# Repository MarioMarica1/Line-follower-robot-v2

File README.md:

# Line Follower Robot v2 · God of Cheese

Line follower robot hardware for **ROBOTEC UPT 2027**. This repository contains the **God of Cheese** KiCad project, its custom libraries, mechanical models, and existing fabrication exports.

The design includes an **ESP32-S3**, a **DRV8833** motor driver, a buck converter, battery connection, slide switch, and motor/sensor connections. Firmware is not included in this repository.

## PCB

| Front | Back (mirrored) |
| :---: | :---: |
|  |  |

These previews are generated from the committed PCB and show copper, silkscreen, and board outline.

## Schematic

[View or download the schematic PDF](docs/schematic.pdf).

## Open the project

1. Clone or download the entire repository.
2. Install **KiCad 10.0 or newer** with its standard symbol, footprint, and 3D model libraries.
3. Open [`God_of_cheeseLFR.kicad_pro`](God_of_cheeseLFR.kicad_pro) in the KiCad Project Manager.
4. Open the schematic or PCB from that project.

Designed in **KiCad 10.0**. Project-specific libraries use `${KIPRJMOD}` paths so the project can be opened from a different computer.

## Repository contents

| Path | Contents |
| --- | --- |
| `God_of_cheeseLFR.kicad_pro` | Main project and design settings |
| `God_of_cheeseLFR.kicad_sch` | Circuit schematic |
| `God_of_cheeseLFR.kicad_pcb` | Two-layer PCB layout |
| `*.pretty/` | Custom footprints, including board artwork |
| `symbols/` | Custom symbol libraries recovered from the schematic's embedded symbols |
| `3dmodels/` | STEP, STL, and SolidWorks mechanical assets |
| `fp-lib-table`, `sym-lib-table` | Portable project library tables |
| `docs/` | PCB previews, schematic PDF, and validation reports |
| `production/` | Existing Gerber archive, BOM, positions, designators, and IPC netlist |

## Design status

This is a hardware design snapshot. See [the validation notes](docs/validation.md) for checks run before publication and the outstanding findings.

The updated schematic includes the input supply `PWR_FLAG` and passes ERC with **0 errors**; 19 connection-grid warnings remain.

The files in `production/` and `Gerber/` are preserved exports supplied with the project; they were **not regenerated** for this upload and their correspondence to the current PCB has not been established. Review the current design and regenerate fabrication outputs before ordering boards. Some BOM entries still contain generic values and empty supplier part numbers.

Local backups, autosaves, editor history, caches, locks, and per-user KiCad settings are excluded from version control.

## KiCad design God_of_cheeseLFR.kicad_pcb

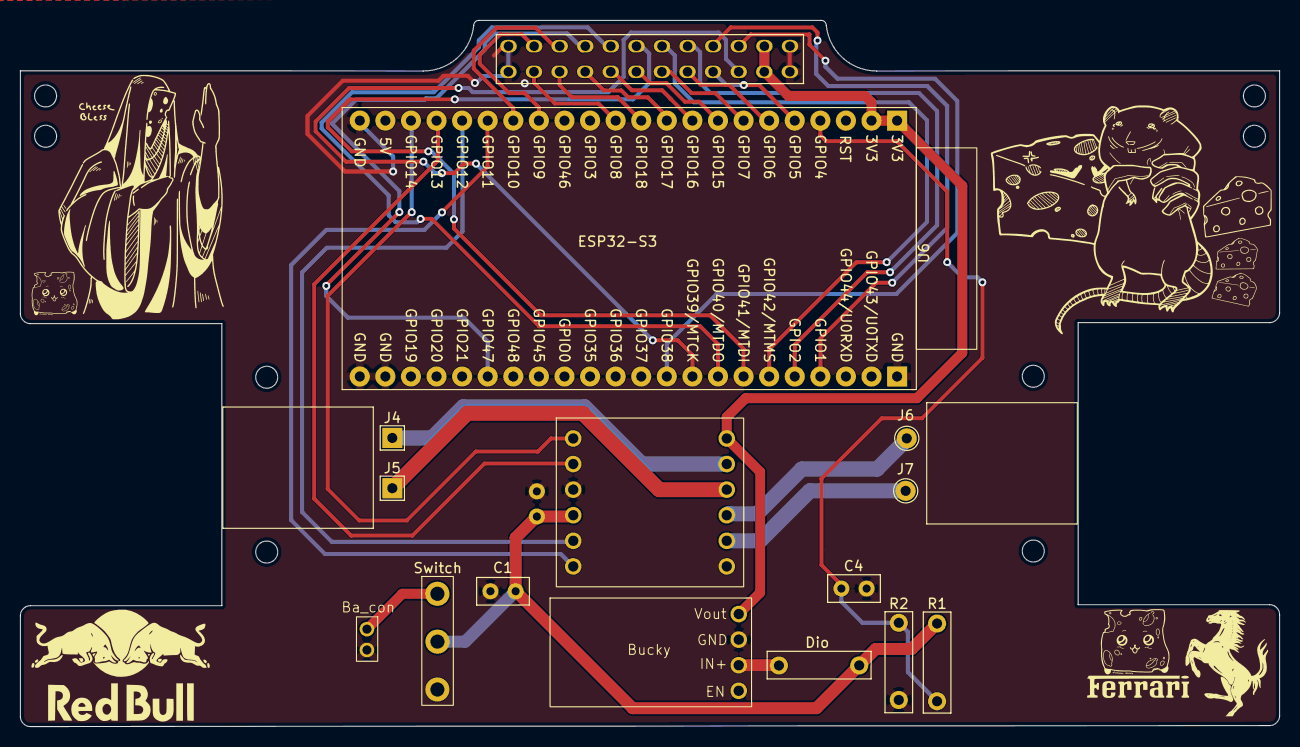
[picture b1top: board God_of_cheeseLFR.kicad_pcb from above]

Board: 2 copper layers, 125.0 x 70.1 mm, 16 parts (1 on the bottom side), 32 nets.

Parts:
Ba_con: B2B-PH-K-S__LF__SN_; Bat_con
Bucky: Buck_converter
C1: C_Polarized; C_Disc_D5.0mm_W2.5mm_P2.50mm
C3, C4: C; C_Disc_D5.0mm_W2.5mm_P2.50mm
DRV8833: DRV8833
Dio: D; C_Disc_D5.0mm_W2.5mm_P2.50mm
J3: Conn_02x12_Row_Letter_Last; 2x12 conn
J4: MOT A 2; TestPoint_THTPad_2.0x2.0mm_Drill1.0mm
J5: MOT A 1; TestPoint_THTPad_2.0x2.0mm_Drill1.0mm
J6: MOT B 1; TestPoint_THTPad_D2.0mm_Drill1.0mm
J7: MOT B 2; TestPoint_THTPad_D2.0mm_Drill1.0mm
R1: 100k; C_Disc_D5.0mm_W2.5mm_P2.50mm
R2: 33k; C_Disc_D5.0mm_W2.5mm_P2.50mm
Switch: SS12D00G3; SW_Slide-03_Wuerth-WS-SLTV_10x2.5x6.4_P2.54mm
U6: ESP32-S3; YD-ESP32-S3

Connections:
+3V3: Bucky.3 (OUT+), DRV8833.7 (EEP), J3.2a, J3.2b, U6.1 (3V3), U6.2 (3V3)
/AIN1: DRV8833.6 (IN1), U6.17 (GPIO11)
/AIN2: DRV8833.5 (IN2), U6.18 (GPIO12)
/BAT_LEVEL: C4.1, R1.2, R2.1, U6.4 (GPIO4)
/BIN1: DRV8833.2 (IN3), U6.19 (GPIO13)
/BIN2: DRV8833.1 (IN4), U6.20 (GPIO14)
/EVEN: J3.3a, U6.35 (GPIO38)
/MOT_A_1: DRV8833.8 (OUT1), J4.1 (1_1)
/MOT_A_2: DRV8833.9 (OUT2), J5.1 (1_1)
/MOT_B_1: DRV8833.10 (OUT3), J6.1 (1_1)
/MOT_B_2: DRV8833.11 (OUT4), J7.1 (1_1)
/ODD: J3.3b, U6.36 (GPIO39)
/SEN1: J3.4b, U6.5 (GPIO5)
/SEN2: J3.4a, U6.41 (GPIO1)
/SEN3: J3.5b, U6.6 (GPIO6)
/SEN4: J3.5a, U6.40 (GPIO2)
/SEN5: J3.6b, U6.7 (GPIO7)
/SEN6: J3.6a, U6.39 (GPIO42)
/SEN7: J3.7b, U6.8 (GPIO15)
/SEN8: J3.7a, U6.38 (GPIO41)
/SEN9: J3.8b, U6.9 (GPIO16)
/SEN10: J3.8a, U6.37 (GPIO40)
/SEN11: J3.9b, U6.10 (GPIO17)
/SEN12: J3.9a, U6.28 (GPIO47)
/SEN13: J3.10b, U6.11 (GPIO18)
/SEN14: J3.10a, U6.15 (GPIO9)
/SEN15: J3.11b, U6.12 (GPIO8)
/SEN16: J3.11a, U6.16 (GPIO10)
/VBAT_RAW: Ba_con.1, Switch.3 (NO)
GND: Ba_con.2, Bucky.4 (GND), C1.2, C3.1, C4.2, DRV8833.3 (GND), J3.1a, J3.1b, J3.12a, J3.12b, R2.2, U6.22 (GND), U6.23 (GND), U6.24 (GND), U6.44 (GND)
unnamed: Bucky.1 (IN+), Dio.1 (K)
VBAT: C1.1, C3.2, DRV8833.4 (VCC), Dio.2 (A), R1.1, Switch.2 (COM)
